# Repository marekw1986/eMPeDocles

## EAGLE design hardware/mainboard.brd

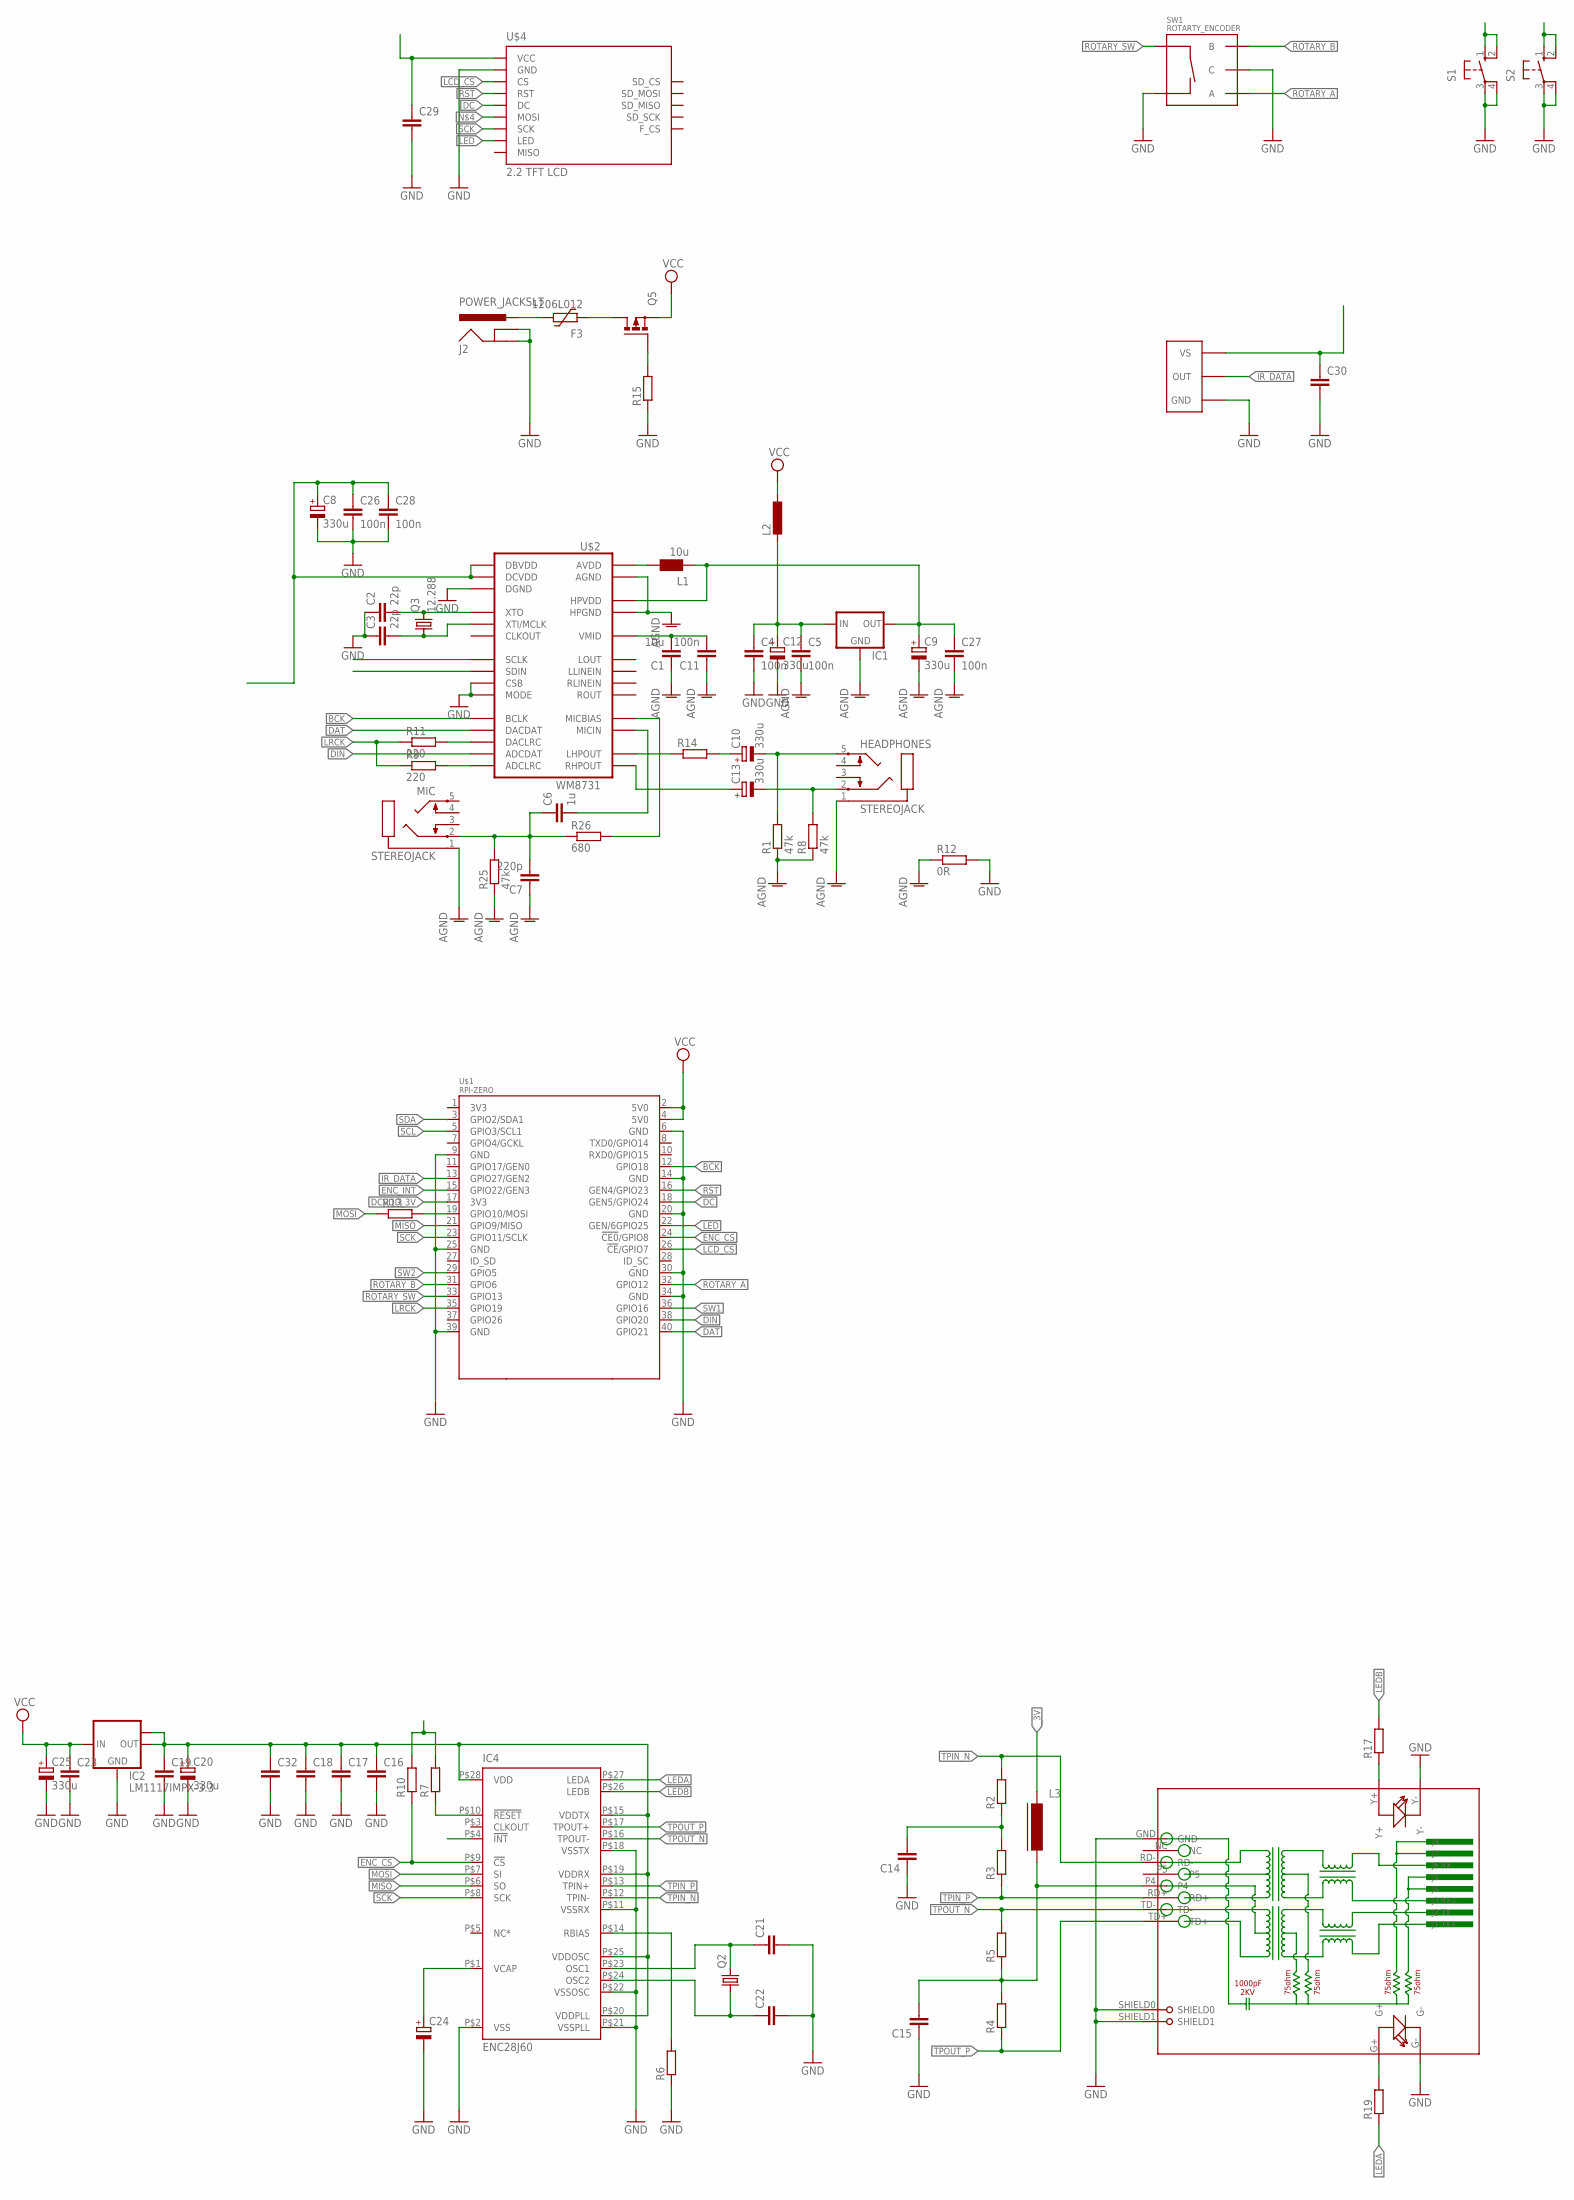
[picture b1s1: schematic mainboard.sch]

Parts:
C1: 10u; C0603
C2, C3: 22p; C0603
C4, C5, C11, C26, C27, C28: 100n; C0603
C6: 1u; C0603
C7: 220p; C0603
C8, C9, C12, C20, C25: 330u; SMC_B
C10, C13: 330u; E3,5-8
C14, C15, C19, C21, C22, C23, C29, C30: C-EUC0603; C0603
C16, C17, C18, C32: C-EUC0402; C0402
C24: CPOL-EUSMCA; SMC_A
F3: 1206L012; 1206L
HEADPHONES: STEREOJACK; STX3100
IC1: 78LXXREV; 78LXX_REV
IC2: LM1117IMPX-3.3; SOT223
IC4: ENC28J60; TSSOP28W
J2: POWER_JACKSLT; POWER_JACK_SLOT
L1: 10u; WE-KI_0805_B
L2: L-EU0204/7; 0204/7
L3: FERRITE-0805; FB805
MIC: STEREOJACK; STX3100
Q2: CRYSTALHC49S; HC49/S
Q3: 12.288; HC49U70
Q5: P-MOSFET-SO8; SO-08
R1, R8, R25: 47k; R0603
R2, R3, R4, R5, R13, R15, R17, R19: R-EU_R0603; R0603
R6, R7: R-EU_0204/7; 0204/7
R9: 220; R0402
R10: R-EU_0204/5; 0204/5
R11: 220; R0603
R12: 0R; R0805
R14: R-EU_R1206; R1206
R26: 680; R0603
RJ1: HR911105A
S1, S2: 40-XX; B3F-40XX
SW1: ROTARTY_ENCODER; ROTARY_ENC_PLAIN
U$1: RPI-ZERO; RASPBERRYPI_BASTELSTUBE_V13_RASPI_BOARD_B+_FULL
U$2: WM8731; 28-SSOP
U$4: 2.2_TFT_LCD
U$5: TSOP312XVERTICAL; TSOP312X_VERT

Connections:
AGND: C1.1, C5.2, C7.1, C9.-, C11.1, C27.2, HEADPHONES.1, IC1.GND, MIC.1, R1.1, R8.1, R12.1, R25.1, U$2.P$11 (HPGND), U$2.P$15 (AGND)
BCK: U$1.12 (GPIO18), U$2.P$3 (BCLK)
DAT: U$1.40 (GPIO21), U$2.P$4 (DACDAT)
DC: U$1.18 (GEN5/GPIO24), U$4.DC
DCVDD_3V: C8.+, C26.1, C28.1, R7.2, R10.2, U$1.17 (3V3), U$2.P$1 (DBVDD), U$2.P$27 (DCVDD)
DIN: U$1.38 (GPIO20), U$2.P$6 (ADCDAT)
ENC_CS: IC4.P$9 (!CS), R10.1, U$1.24 (!CE0!/GPIO8)
ENC_INT: IC4.P$4 (!INT), U$1.15 (GPIO22/GEN3)
ENC_RST: IC4.P$10 (!RESET), R7.1
GND: C2.1, C3.1, C4.2, C8.-, C12.-, C14.1, C15.1, C16.2, C17.2, C18.2, C19.2, C20.-, C21.2, C22.2, C23.2, C24.-, C25.-, C26.2, C28.2, C29.2, C30.2, C32.2, IC2.1 (GND), IC4.P$2 (VSS), IC4.P$11 (VSSRX), IC4.P$18 (VSSTX), IC4.P$21 (VSSPLL), IC4.P$22 (VSSOSC), J2.GND@1 (GNDBREAK), J2.GND@2 (GND), R6.1, R12.2, R15.1, RJ1.G-, RJ1.GND, RJ1.SHIELD0, RJ1.SHIELD1, RJ1.Y-, S1.3, S1.4 (P1), S2.3, S2.4 (P1), SW1.C, SW1.SW-, U$1.6 (GND), U$1.9 (GND), U$1.14 (GND), U$1.20 (GND), U$1.25 (GND), U$1.30 (GND), U$1.34 (GND), U$1.39 (GND), U$2.P$21 (MODE), U$2.P$22 (CSB), U$2.P$28 (DGND), U$4.GND, U$5.1 (GND)
IR_DATA: U$1.13 (GPIO27/GEN2), U$5.3 (OUT)
LCD_CS: U$1.26 (!CE!/GPIO7), U$4.CS
LED: U$1.22 (GEN/6GPIO25), U$4.LED
LEDA: IC4.P$27 (LEDA), R19.1
LEDB: IC4.P$26 (LEDB), R17.2
LRCK: R9.1, R11.1, U$1.35 (GPIO19)
MISO: IC4.P$6 (SO), U$1.21 (GPIO9/MISO)
MOSI: IC4.P$7 (SI), R13.1
unnamed: R26.2, U$2.P$17 (MICBIAS)
unnamed: C14.2, R2.1, R3.2
unnamed: R14.1, U$2.P$9 (LHPOUT)
unnamed: R13.2, U$1.19 (GPIO10/MOSI), U$4.MOSI
unnamed: F3.2, Q5.5 (D), Q5.6 (D), Q5.7 (D), Q5.8 (D)
unnamed: C15.2, L3.2, R4.2, R5.1, RJ1.P4
unnamed: C4.1, C5.1, C12.+, IC1.IN, L2.2
unnamed: C10.+, R14.2
unnamed: F3.1, J2.PWR
unnamed: C2.2, Q3.2, U$2.P$26 (XTO)
unnamed: IC4.P$14 (RBIAS), R6.2
unnamed: C3.2, Q3.1, U$2.P$25 (XTI/MCLK)
unnamed: C10.-, HEADPHONES.5, R1.2
unnamed: C21.1, IC4.P$23 (OSC1), Q2.2
unnamed: C22.1, IC4.P$24 (OSC2), Q2.1
unnamed: Q5.4 (G), R15.2
unnamed: C24.+, IC4.P$1 (VCAP)
unnamed: R17.1, RJ1.Y+
unnamed: R19.2, RJ1.G+
unnamed: C9.+, C27.1, IC1.OUT, L1.2 (1), U$2.P$8 (HPVDD)
unnamed: R11.2, U$2.P$5 (DACLRC)
unnamed: R9.2, U$2.P$7 (ADCLRC)
unnamed: C1.2, C11.2, U$2.P$16 (VMID)
unnamed: C13.-, HEADPHONES.2, R8.2
unnamed: L1.1 (2), U$2.P$14 (AVDD)
unnamed: C13.+, U$2.P$10 (RHPOUT)
unnamed: C6.2, U$2.P$18 (MICIN)
unnamed: C6.1, C7.2, MIC.2, R25.2, R26.1
ROTARY_A: SW1.A, U$1.32 (GPIO12)
ROTARY_B: SW1.B, U$1.31 (GPIO6)
ROTARY_SW: SW1.SW+, U$1.33 (GPIO13)
RST: U$1.16 (GEN4/GPIO23), U$4.RST
SCK: IC4.P$8 (SCK), U$1.23 (GPIO11/SCLK), U$4.SCK
SCL: U$1.5 (GPIO3/SCL1), U$2.P$24 (SCLK)
SDA: U$1.3 (GPIO2/SDA1), U$2.P$23 (SDIN)
SW1: S1.1 (S), S1.2 (S1), U$1.36 (GPIO16)
SW2: S2.1 (S), S2.2 (S1), U$1.29 (GPIO5)
TPIN_N: IC4.P$12 (TPIN-), R2.2, RJ1.RD-
TPIN_P: IC4.P$13 (TPIN+), R3.1, RJ1.RD+
TPOUT_N: IC4.P$16 (TPOUT-), R5.2, RJ1.TD-
TPOUT_P: IC4.P$17 (TPOUT+), R4.1, RJ1.TD+
VCC: C23.1, C25.+, IC2.3 (IN), L2.1, Q5.1 (S), Q5.2 (S), Q5.3 (S), U$1.2 (5V0), U$1.4 (5V0)
_3V: C16.1, C17.1, C18.1, C19.1, C20.+, C29.1, C30.1, C32.1, IC2.2 (OUT), IC2.TAB (OUT1), IC4.P$15 (VDDTX), IC4.P$19 (VDDRX), IC4.P$20 (VDDPLL), IC4.P$25 (VDDOSC), IC4.P$28 (VDD), L3.1, U$4.VCC, U$5.2 (VS)

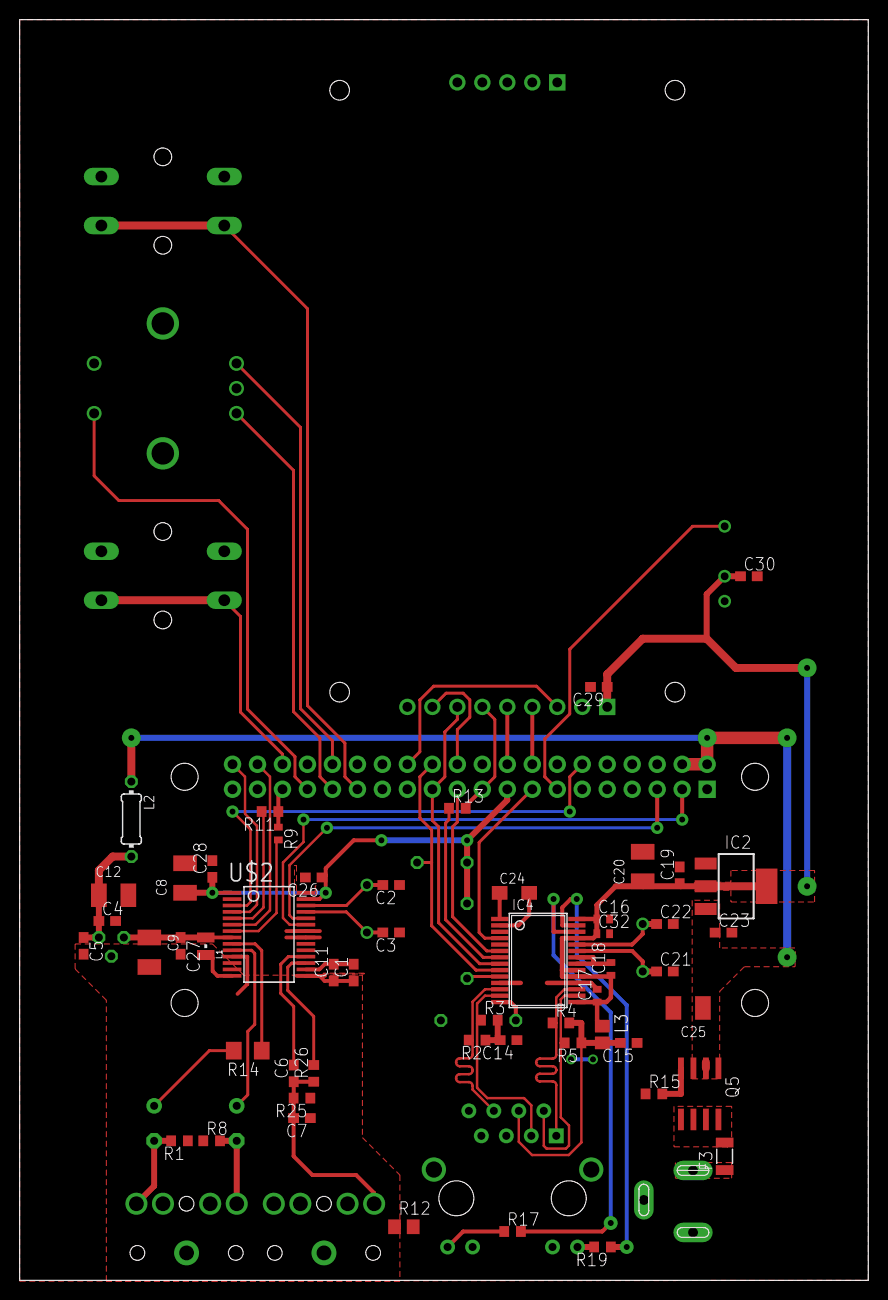
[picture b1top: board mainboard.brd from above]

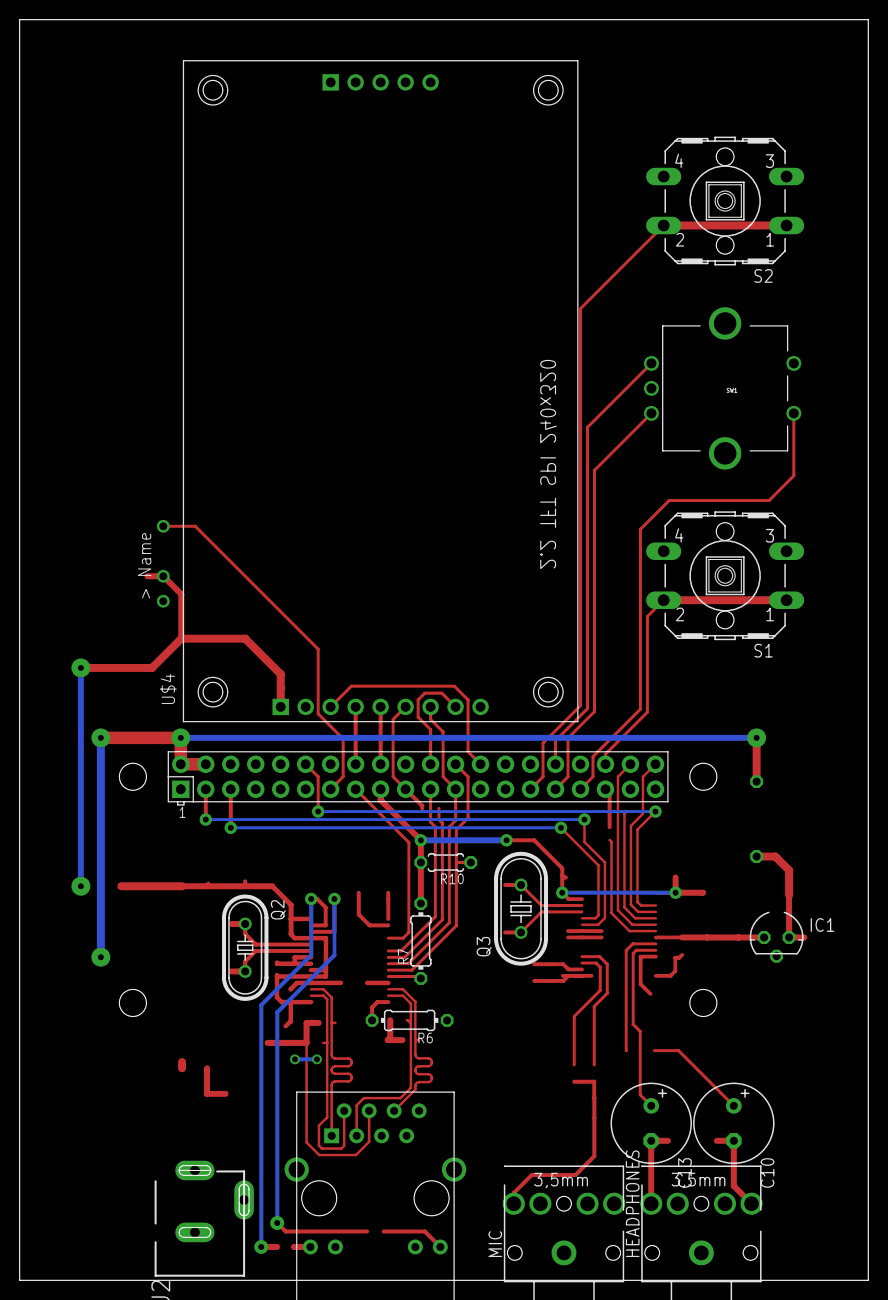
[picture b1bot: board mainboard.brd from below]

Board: 2 copper layers, 86.3 x 128.2 mm, 71 parts (18 on the bottom side), 61 nets.

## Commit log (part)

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2026-06-28 Generated prototype for UI aded
2026-06-28 UI updated
2026-06-28 cleanup
2026-06-29 Menu added to UI
2026-06-30 Split

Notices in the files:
parts and their libraries:
SparkFun-Connectors: Licensing: Creative Commons ShareAlike 4.0 International - https://creativecommons.org/licenses/by-sa/4.0
